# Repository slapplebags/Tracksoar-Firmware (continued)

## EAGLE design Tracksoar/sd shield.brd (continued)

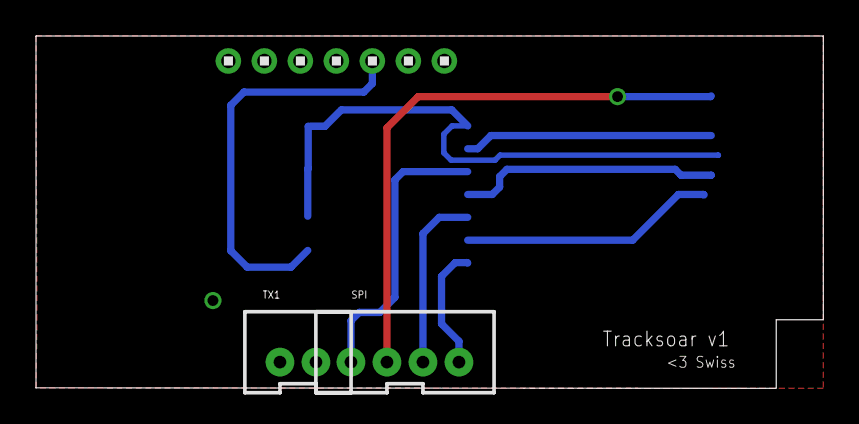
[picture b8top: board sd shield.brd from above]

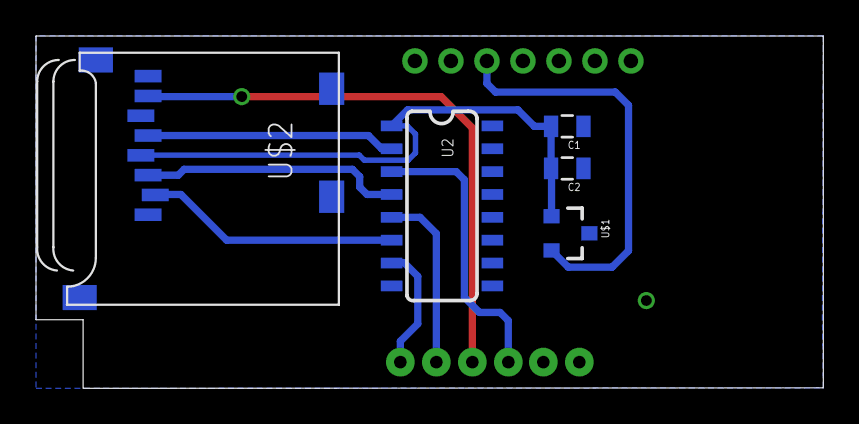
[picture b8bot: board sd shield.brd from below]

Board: 2 copper layers, 43.7 x 19.6 mm, 9 parts (5 on the bottom side), 10 nets.

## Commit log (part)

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2014-11-19 Arduino APRS tracker
    An improved / smaller trackduino clone.
2014-11-19 reset switch
    added a reset switch and improved RF ground fill.
2014-11-19 added crystal on atmega 328p
    added a 16mhz crystal to the atmega 328p / arduino. Cleaned up the
    schematic a bit.
2014-11-19 added .pdf of schematic
2014-11-19 fixed missing vcc / ground connections
    missed AVCC and AGND
2014-11-20 Removed all unnecessary files and added their extensions to .gitignore
2014-11-20 Separated license from rest of read
2014-11-20 dumb things
2014-11-20 swapped crystal for smaller resonator
2014-11-21 removed level shifters
    removed unnecessary 5v level shifters from boards.
2014-11-21 re-routed micro board
2014-11-21 missed a wire
2014-11-21 removed via from antenna ground
2014-11-22 capacitors do not fit underneath things
2014-11-22 minor fixes
    boards ordered.
2014-11-22 fixed consistency error on last commit
2014-11-23 stuff
2014-11-23 Protoboards Rev 1
    revision 1 prototype boards, these have been sent to osh park for
    manufacture. Parts have been ordered to test these boards.
2014-11-24 Revert 658c1f1..8864008
    This rolls back to commit 658c1f11e5b9c3d0ac6cf8412ef3704af54d539a.
2014-11-24 Revert "Protoboards Rev 1"
    This reverts commit 8864008ccbdc4df3da8dbd79e6a63e8a5caf342f.
2014-11-24 Revert 8864008..532531c
    This rolls back to commit 8864008ccbdc4df3da8dbd79e6a63e8a5caf342f.
2014-11-24 Revert 658c1f1..c6afc34
    This rolls back to commit 658c1f11e5b9c3d0ac6cf8412ef3704af54d539a.
2014-11-24 Revert 8864008..40b68b5
    This rolls back to commit 8864008ccbdc4df3da8dbd79e6a63e8a5caf342f.
2014-11-24 Revert 8864008..c721b65
    This rolls back to commit 8864008ccbdc4df3da8dbd79e6a63e8a5caf342f.
2014-11-24 Revert "Revert 8864008..c721b65"
    This reverts commit 1e770fae9d4fe301bf64f6128993cadc941d7714.
2014-11-24 Revert 8864008..7e8a1de
    This rolls back to commit 8864008ccbdc4df3da8dbd79e6a63e8a5caf342f.
2014-11-25 Revert 8864008..d1c2883
    This rolls back to commit 8864008ccbdc4df3da8dbd79e6a63e8a5caf342f.
2014-11-25 Revert 3403df9..f4310d6
    This rolls back to commit 3403df9037498db32c64046a9108877ce30486f0.
2014-11-25 micro board broken
    The bed file on the micro board was broken, rolled back to a working
    commit and moved it to this good commit.
2014-12-03 added ublox530 eagle footprint
    eagle cad ublox 530 eagle cad footprint, still need pin naming
2014-12-04 fixed uc530 library
    fixed pin names / assignments and cleaned up the package a bit.
2014-12-04 cleaned up extra files
2014-12-06 rearranging
2014-12-07 added pico and micro test boards
2014-12-09 minor fixes to smallest boards
2014-12-15 updated micro to mk1
    to match the mini
2014-12-29 new micro board with integrated sensors
2015-01-05 traccino micro sensor
2015-01-12 trackuino micro sensor mk2
    replaced 5v LDO regulator with boost regulator for operation from 2 AA
    or AAA batteries.
2015-01-12 tracking sensor mk2 added nets
2015-01-25 sensor mk2 fixes
    fixed a short on the boost output and serial RX
2015-01-25 fixed ground plane bit
2015-01-28 DRC check
    ran osh park DRC check and resolved errors.
2015-01-28 boost converter fix
    fixed external component placement and added some silkscreen
2015-02-12 chip gps antenna
2015-02-16 replaced inductor
    the 0805 inductor was getting way too hot due to being run well beyond
    saturation. replaced with a 1812 inductor
2015-02-17 added chip antenna latest version
2015-03-15 Update LICENSE
2015-03-15 replaced sht15
2015-03-15 rerouted for sht21
2015-03-16 sht21 routing
2015-03-18 sensor chip production
2015-03-18 chip gps routing
2015-03-26 solar board routing
2015-03-26 solar replace antenna
2015-03-26 pdf brds created and chip board shortened
2015-03-27 fixed overlaps on solar
2015-03-27 moving old boards to archive
2015-03-29 missing i2c trace on chip
    fixed missing i2c trace on the chip board
2015-03-30 moved via near ublox pin 1
    via near ublox pin 1 is too close for comfort. Moved it slightly
2015-04-05 Removed "Archive" directory
2015-04-05 Removed other branches files from this branch
2015-04-05 Yep, removed other branches files from this branch (last one, I promise)
2015-04-05 Added 10mm grid based fixturing holes to board
2015-04-10 new firmware added
    added firmware to accept the max 8 gps module
2015-04-11 Consider $GNGGA and $GNRMC as $GPGGA and $GPRMC.
2015-04-12 removed unneeded info from readme
2015-04-14 Moved all boards to origin
    Moved all the boards such that the lower left most corner is at the
    origin.
2015-04-14 lined up 12c / spi headers
    lined up api and i2c headers between the chip, u.fl, and solar versions
    of the board.
2015-04-25 tx rx 2mm headers
    replaced .1” serial headers on chip and non chip version with 2mm
    headers
2015-04-25 Allow to compile from Arduino 1.6
2015-04-27 Removed old firmware files
    Removed old firmware files that are not up to date.
2015-04-29 Created Mux Test
    Created a new board to see if the MUX will fit in two layers
2015-04-29 Removed Via From Under MCU
    Removed a via from under the ATMEGA328P to prevent any potential
    shorts.
2015-05-13 added ground planes on inner layers
    added ground planes on inner layers and ran drc.
2015-05-19 Standardized round via
    Changed all via on production boards to round, and moved hidden via on
    solar board out from under the atmega. Also fixed bom to specify
    max-m8q gps.
2015-05-20 updating ignore
2015-05-20 moved sda wire on chip
    moved sda wire on chip board to make its path a little cleaner
2015-05-21 created test folder
    created a test folder for unproven boards and schematics, moved the mux
    test and solar versions to test.
2015-05-21 removed pdfs
    removed outdated pdfs
2015-05-22 Tightened up traces, altered gnd pours. Enlarged border.
2015-05-22 resolved DRC errors
    Resolved DRC errors on both versions of the board.
2015-05-22 Simplified Ground Polygons
    simplified ground polygons and further DRC error resolutions.
2015-05-26 Updated silkscreen name
    changed name on silkscreens.
2015-06-03 Moved mix test LED
    changed the schematic on the mux test to move the pulse per second LED
    to the correct area on the schematic.
2015-06-11 Added Libraries
    moved uc530 to libraries folder, added 2 libraries for 2 meter
    transmitter
2015-06-12 added 2 meter transmitter
    added a test 2 meter transmitter. It is very rough and needs a couple
    of caps after the final amplifier.
2015-06-21 new shield
    added an updated shield for the chip tracksoar.
2015-06-22 Fixed chip shield
    added a cutout to prevent obstructing the GPS chip antenna. Removed an
    extra ground trace form the chip board.
2015-06-23 created a programming shield
    added a chip shield programming shield
2015-06-23 ISP 5v short removed
    removed a short from the ISP reset pin to 5v
2015-06-23 2 meter rx fixes
    added ground pours and 4 pin header to the 2 meter rx for a test board.
2015-06-28 added breakout shield
    added a breakout chip shield
2015-07-04 moved silkscreen sig
    moved the silkscreen signature to be visible.
2015-07-09 moved ground via
    moved ground via near gps module.
2015-07-30 SHT21.cpp loop fix
    fixed an issue in the SHT21.cpp code that will cause the board to not
    transmit if the SHT21 fails to provide data.
2015-08-16 Clean up unhelpful sketch files, and rename sketch.
2015-08-16 Time out on attempting to configure GPS after 1 minute.
2015-08-16 new sensor test
    new sensor test
2015-08-23 Added logo
    added silkscreen logo
2015-08-30 added imbue shield
    added an IMU shield with a 9 dof imu
2015-09-15 Shield Updates
    added sd storage shield, added fetid chip to programming shield. Moved
    test boards to correct folder.
2015-09-15 renamed boards
    renamed boards to tracksoar
2015-09-20 replace headers
    replaced 2.54mm headers on all production boards with 2mm headers to
    resolve daughter board issues.
2015-10-02 mirrored sd shield
    flipped components on the sd shield to be on the correct side
2015-10-09 Rounded corners
    Added rounded corners to the tracksoar v1
2015-10-09 replaced shield
    replace shield with an updated shield template
2015-10-09 shield silkscreen fix
    minor fix on shield template silk screen
2015-10-14 removed old shields
    removed square shields and added values to shield passives
2015-10-15 removed components below gps
    Removed the step up circuit components below the gps receiver and added
    vias to prevent any interference
2015-12-05 initial route with attiny84
    initial routing of the attiny84 based board.
2016-01-19 test radio build
2016-01-24 fixed shield footprint
2016-01-24 replaced sd with eeprom
    the atmega328p does not have enough SRAM to handle the Trackuino duties
    and SD read / write. It has been replace with an ST Micro M24M02 2Mb
    eeprom. This will result in much less RAM usage, a smaller BOM, lower
    cost, and lower power usage. However it also means we lose portability
    of storage and easy computer interfacing. We’ll look at revising this
    in future versions.
2016-01-24 tracksoar firmware optimizations for sd
    trying to cram an SD library into 2k of sram with the aprs stuff
2016-02-07 fixed BMP180 pressure sensor output
    fixed an issue with the pressure reported by the BMP180
2016-05-05 tracksoar v1.2
    Tracksoar v1.2, replaced EOL’d BMP180 and SHT21 sensors with combo
    BME280 sensor. Added an active GPS version of the board for those using
    FPV modules utilizing 1.5GHZ links.
2016-06-01 resolved 1.6.5+ compiling issues
    resolved issues in afsk_avr.cpp / h that prevented the firmware from
    compiling in 1.6.5+
2016-06-01 tracksoar v1.1 eeprom
    added the tracksoar eeprom firmware
2016-06-01 removed old firmware
    removed old firmwares
2016-06-05 Initial V2 routing
    first attempt at routing the V2 Tracksoar
2016-06-06 Removed v1.1 headers
    removed the v1.1 headers to simplify layout.
2016-09-04 Added hardware version defines, added support for BME280 sensor, added version reporting to APRS comment string
2016-09-04 Added comment about adding SPI.h to main ino file
2016-09-04 Removed lock files from commits
2016-09-04 Removed old lock files from repo
2017-04-15 added back the eeprom writing code
2017-04-15 fixed name confilict added interval var and include issues
2017-04-15 fixed type name
2017-04-19 Tracksoar v2 rev2
    finalized routing, added 3v access to programming header
2017-04-19 tracksoar v2 rev3
    added GPIO and analog pins to new header with i2c.
2017-04-24 tracksoar v2 rev5
    added ferrite to 5v output on boost converter. Added 4.7k resistor
    between Vin and AREF to provide battery voltage monitoring.
2017-04-27 Moved Test Boards
    Moved the test boards folder to the hardware repo.
2017-06-01 Added Watch Dog Timer
    Added a watchdog timer to prevent locking up during reads of the BME280
    sensor via i2c.
2017-06-03 added platformio build system and a basic circleci config
2017-06-03 added non-working radio.cpp to see how ci hangles bad PRs
2017-06-03 this is a test thing to break the things
2017-06-03 more breaking
2018-03-10 added v1.1.2 firmware
    added v1.1.2 firmware
2018-03-15 Add additional board target, everything is fire.
2018-03-16 Split out files for the 328/32u4. Drop pic32 stuff.
2018-03-16 Use proper extensions.
2018-03-16 It builds and links ok?
2018-03-16 Mention timer 4.
2018-03-18 Seems to be operating correctly now.
2018-03-24 Fix GPS.
2018-03-24 Rename the serial ports to something that's actually helpful.
2018-03-24 Better sensor debug, some formatting.
2018-03-24 Battery status read-back should now work.
2018-03-25 Fix derp.
2018-03-25 added ignore
    added mac garbage to ignore
